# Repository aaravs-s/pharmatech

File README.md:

# Team Pharmatech

Boilerplate repository structure for a pill compounding machine project.

## Top-level areas
- `cad/` - mechanical and enclosure design files
- `firmware/` - embedded software and configuration
- `electronics/` - schematic, PCB, and component documentation

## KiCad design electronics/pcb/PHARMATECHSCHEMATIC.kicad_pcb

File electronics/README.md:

# Electronics

Electrical design artifacts for control, power, and interface circuitry.

## Layout
- `schematics/` - source schematic files
- `pcb/` - PCB layout files and fabrication outputs
- `bom/` - bill of materials and sourcing sheets
- `simulation/` - circuit simulation setups and outputs
- `docs/` - electronics-specific engineering notes

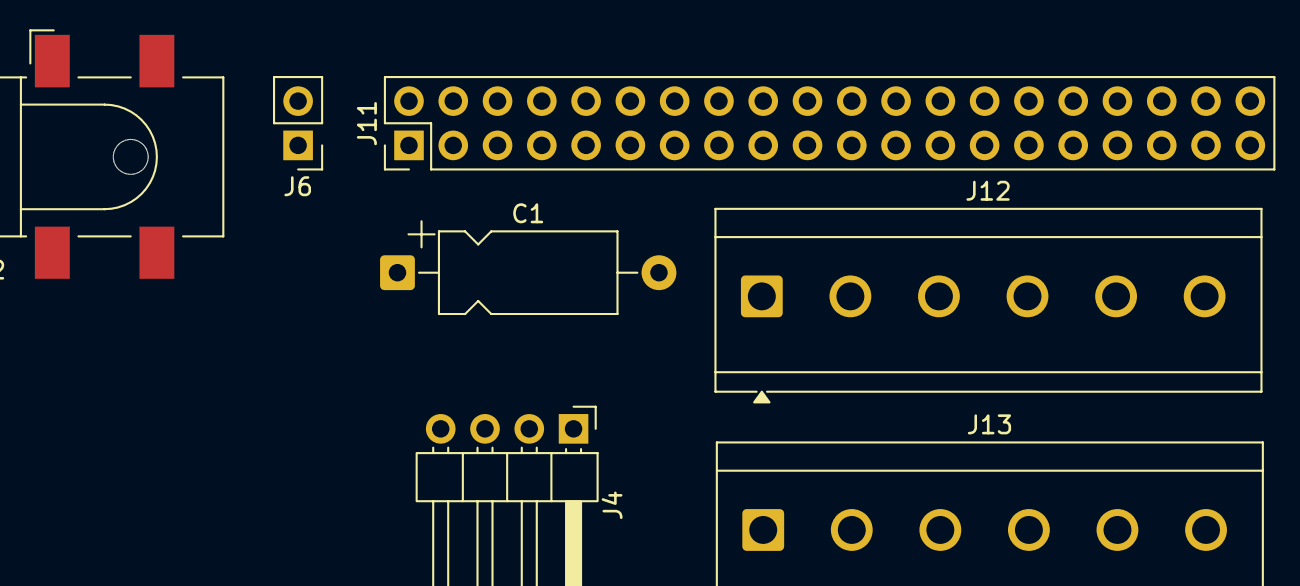
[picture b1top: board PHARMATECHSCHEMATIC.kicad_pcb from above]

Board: 2 copper layers, 7 parts (0 on the bottom side), 6 nets, no tracks yet.

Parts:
C1: C; CP_Axial_L10.0mm_D4.5mm_P15.00mm_Horizontal
J2: Barrel_Jack_MountingPin; BarrelJack_CLIFF_FC681465S_SMT_Horizontal
J4: Conn_01x04; PinHeader_1x04_P2.54mm_Horizontal
J6: USB BUCK CONVERTER FOR PI; PinHeader_1x02_P2.54mm_Vertical
J11: RASPBERRY_PI_4; PinHeader_2x20_P2.54mm_Vertical
J12: MOTOR1; TerminalBlock_CUI_TB007-508-06_1x06_P5.08mm_Horizontal
J13: MOTOR2; TerminalBlock_CUI_TB007-508-06_1x06_P5.08mm_Horizontal

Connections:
+24V: C1.1, J2.2, J6.1, J12.5, J13.5
/DIR1: J11.3, J12.3, J13.4
/ENA1: J11.5, J12.4
/ENA2: J11.13, J13.3
/PLS1 (STEP): J11.1, J12.2, J13.2
GND: C1.2, J2.1, J6.2, J12.1, J12.6, J13.1, J13.6

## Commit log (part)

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2026-06-09 Initial plan
2026-06-09 Add boilerplate CAD firmware electronics structure
2026-06-22 Rename journal.md to JOURNAL.md
2026-06-27 Add stepper motor control code using AccelStepper
